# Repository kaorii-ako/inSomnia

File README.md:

# inSomnia

An adaptive, context-aware wake clock. Instead of firing at a fixed timestamp, it wakes you inside a window at a moment you are already stirring — and if you got up before the window even opened, it stays quiet.

Built for [Hack Club Forge](https://forge.hackclub.com). Firmware-first, fully offline after WiFi time sync, no cloud service, no audio leaves the device.

---

## What it actually does

| Situation | Behaviour |
|---|---|
| You're already up before the window opens | Alarm is suppressed for the day and logged as "skipped — you were already up" |
| You're carrying sleep debt | The gentle wake is held back by up to 15 min so an early stir doesn't cost you the lie-in. **The hard deadline never moves.** |
| You start stirring inside the window | Gentle wake begins immediately — soft tone ramping up over several minutes |
| You sleep right through to the hard deadline | Full-intensity alarm, no more waiting |
| A sensor dies or is unplugged | **Failsafe**: degrades to a plain fixed-time alarm at the deadline. It never fails silent. Even with no WiFi it runs on an internal fallback clock. |

### Why I made it

I hate being ripped out of deep sleep at 06:50 exactly when I was finally sleeping well, and I also hate my phone blaring when I’m already in the kitchen making coffee. Both are the same bug: a clock that knows time but not context. I wanted a clock that knows *whether I'm in bed and moving* — easily measurable with a thermal array — and uses that to pick a kinder moment inside a window, or to stay quiet if I’m already up. I built it for myself, and because a believable demo needs honest numbers, not "AI" marketing.

### The 12 keys

| | col 1 | col 2 | col 3 | col 4 |
|---|---|---|---|---|
| **row 1** (front) | `DISMISS` | `SNOOZE` | `LIGHT` | `SKIP` |
| **row 2** | `OPEN −` | `OPEN +` | `DEAD −` | `DEAD +` |
| **row 3** (back) | `PAGE` | `SOFT` | `LOUD` | `SAVE` |

Row 1 is what you hit half-asleep. Rows 2 and 3 are setup you do awake: move the window and deadline in 5-minute steps, page through status / window / sleep-debt screens, test the alarm, save to flash. Everything is also on the web UI at `http://insomnia.local`.

## How to use it — step by step

1. **Assemble** — Solder the PCB (`hardware/inSomnia.kicad_pcb`, 0805 passives, through-hole tactiles), mount the board on the 4× M2 bosses in `hardware/case/inSomnia_case.FCStd`, plug modules onto headers: J3 ST7735 TFT, J4 INMP441 mic, J5 MLX90640 thermal (aimed at the bed), J7 optional native USB.
2. **Flash** — `cd firmware && pio run -t upload` and `pio device monitor` at 115200. Requires PlatformIO + `espressif32@6.5.0`.
3. **First boot WiFi** — No credentials stored, so it opens AP `inSomnia-setup` (pass `insomnia`). Join it, open `http://192.168.4.1`, pick your network + password. Reboots and appears as `http://insomnia.local` (mDNS). If no WiFi, it still runs on a fallback clock (`*` beside time) and will still alarm at the deadline.
4. **Set your window** — On device: `OPEN ±` and `DEAD ±` move times in 5-min steps, `PAGE` to see them, `SAVE` to flash. Or on web UI: *Settings → Window opens / Hard deadline*.
5. **Sleep** — Place the clock on the nightstand with the thermal aperture aimed at the bed (within ~1.5 m, no wire to the bed). ` roi` in Settings crops the bed region if needed.
6. **Morning** — `DISMISS` stops, `SNOOZE` (= snoozeMin, default 7) resumes as hard alarm, `SKIP` is manual "don't bother tonight". Last night's sleep: `PAGE` → debt screen or web *Last night* card (TST / efficiency / WASO / SOL — labelled as estimates).
7. **Tune** — Web *Settings*: `countScale` is the one calibration — watch *Counts this epoch* overnight, set so quiet epoch ≈ 0; `Body margin` and `in-bed min pixels` for duvet thickness.

## How it decides

One sensor does most of the work:

- **MLX90640 32×24 thermal array**, on the clock, aimed at the bed.
  - *Frame-to-frame change* → a motion index. This is contactless video actigraphy, validated against polysomnography at **Cohen's κ = 0.733**, comparable to a wrist actigraph. It feeds Cole-Kripke.
  - *Warm body-sized region* → **in bed / out of bed**. Far stronger than a PIR, because it can tell you-in-the-bed from a warm object in the room.
  - No wire to the bed, and at 768 pixels you cannot identify a person from it.
- **INMP441 I2S microphone** → RMS level per epoch. A loudness hint that nudges the stirring threshold. It is a level detector, *not* a sound classifier.

An earlier version used a mattress accelerometer. It was dropped because it needs 1–2 m of I2C cable from the nightstand to the bed, and I2C is spec'd to 400 pF (≈1 m at 100 kHz) against cable that runs 100–240 pF/m.

Two separate pieces of logic sit on top, because they answer different questions:

1. **A causal 3-state machine** (asleep / stirring / awake) with hysteresis. It may only look backwards, because it drives the alarm in real time. This is a threshold heuristic — see the honesty section below.
2. **Cole-Kripke (1992)** for the morning report. It needs the two *following* epochs, so it lags 2 minutes and can never drive a live decision.

## Being honest about the "AI"

This matters more than the feature list, so it goes near the top.

**The on-device logic is not AI.** Cole-Kripke is a weighted moving average with a threshold, published in 1992. The 3-state classifier is thresholds plus hysteresis. Calling either one "AI" would be marketing, not engineering.

**Accuracy ceiling.** Actigraphy sleep/wake scoring agrees with clinical polysomnography roughly **78–80%** of the time. But its specificity for *wake* is only **0.35–0.64** — it is much better at spotting sleep than wakefulness. Sound-based staging is no better: the best published smartphone-audio model (HomeSleepNet) gets 76.2% overall and **63.4% on wake epochs**.

That single fact shaped the design. Alarm suppression is the feature most exposed to a wrong "you're awake" call, so it is **not** driven by the sleep classifier. It is driven by `outOfBed()` — no warm mass in the bed region for 3 epochs — which is close to a binary measurement rather than a 64%-accurate inference.

**This is not clinical sleep tracking.** Without EEG there is no true sleep staging. Consumer trackers systematically overestimate sleep and underestimate wake-after-sleep-onset, worst of all for people who sleep badly. The numbers in the app are estimates and are labelled as such.

**One number you must calibrate.** Cole-Kripke's weights assume ActiGraph counts, a proprietary unit. Ours are arbitrary units from your own mattress, so `countScale` in Settings divides ours into that range. The *algorithm* is validated; this *scaling* is not. Watch epoch counts overnight and set it so a quiet epoch lands near zero.

**Posture is not claimed.** The thermal array reports *movement and position*. Classifying sleeping posture under a duvet at 32×24 is a research problem — the published work that does it used an infrared **depth** camera with synthetic blanket augmentation. Movement and position are what the sleep model needs, so that is what is built and that is what it says.

**Sleep debt is an estimate built on an estimate.** Debt is `max(0, need − actual)` summed over a rolling 14 nights, which is the window research finds matters for current impairment (Van Dongen 2003: 6 h/night for 14 days ≈ two nights of total deprivation). But "actual" comes from Cole-Kripke scoring that under-reports wake — so read it as a trend, not a clinical figure.

**No trained model ships yet.** A learned audio or thermal classifier is the obvious next step, but a model needs labelled data and there is no polysomnography ground truth here to validate against. The honest path is to ship the validated heuristic, collect feature data, and only then train.

---

## Hardware

**ESP32-S3-WROOM-1-N16R8** — WiFi + BLE 5, native I2S, 8 MB PSRAM, SIMD for future MFCC work. Chosen over the ESP32-C3 because the C3 has no PSRAM and too few GPIO once an I2S microphone is added.

Schematic, pin map, BOM and wiring notes: **[`hardware/HARDWARE.md`](hardware/HARDWARE.md)**
BOM with pricing: [`hardware/inSomnia_bom.csv`](hardware/inSomnia_bom.csv) — **~$68.62 for 1 unit incl. sensors** (MLX90640 dominates)
Rendered schematic: `hardware/inSomnia_schematic.pdf` and `images/schematic.png`
Gerbers: `hardware/inSomnia_gerbers.zip` + `hardware/fab/`

> The hero image above is a **render** from the actual FreeCAD STL (`hardware/case/inSomnia_case_shell.stl`, 7,628 verts), not a photo — nothing has been fabricated yet. It is built to the same dimensions as the FreeCAD enclosure below, and the board renders come from the actual KiCad files.

### Wiring

*All modules plug onto headers — no soldering to the bed. See `hardware/HARDWARE.md` pin map for the exact GPIO table and `images/routing-front-copper.png` for the routed board.*

| Header | Module | Wires |
|---|---|---|
| J3 1×08 | ST7735 128×160 TFT | SCK 12, MOSI 11, CS 10, DC 9, RST 8, BL 13 (PWM), +3V3/GND |
| J4 1×06 | INMP441 mic (I2S) | BCLK 4, WS 5, DIN 6, +3V3/GND |
| J5 1×05 | MLX90640 32×24 thermal (I2C) | SDA 1, SCL 2 (4.7k pull-ups), +3V3/GND |
| J6 1×03 | Spare / was PIR | +5V, IO14, GND |
| J7 1×04 | Native USB | D- 19, D+ 20 |
| J1 1×02 | Power 5V in | 5V → AMS1117-3.3 → 3V3 |
| J2 1×06 | UART prog | TX/RX + EN/BOOT tactiles SW1/SW2 |

### Enclosure

Parametric case in FreeCAD: **`hardware/case/`** (STEP + STL + `.FCStd`).

- 106 × 86 × 54 mm outer, 2.5 mm walls, 101 × 81 mm cavity for the board
- Wedge profile, display face sloped 44.1°
- **36 × 29 mm display window** — a 1.8" ST7735's *active area* is only ~35 × 28 mm, much smaller than the module outline
- 12 keypad holes cut at the real SW3–SW14 coordinates from the KiCad file
- Thermal aperture, buzzer grille, rear cable exit, regulator vents, 4× M2 bosses aligning with PCB mounting holes (3.2mm NPTH)
- ~58 cm³ ≈ 72 g of PLA at full infill

FreeCAD + STEP + STL:
`hardware/case/inSomnia_case.FCStd` / `inSomnia_case_shell.step` / `inSomnia_case_shell.stl` / `inSomnia_base_plate.step`
Case views: `images/case-iso.png` `images/case-front.png` `images/case-top.png`

The FreeCAD model now embeds the PCB placement so the board sits on the bosses; the Blender render imports the STL directly so they cannot drift (replaced earlier hand-typed dimensions).

Known cosmetic issue: the keypad sits right-of-centre because that is where it is on the PCB. Fixing it means re-laying-out the board; noted for v2.

- 53 components + 4× M2 mounting holes, 41 nets, **schematic ERC clean (0 violations)**
- 100 × 80 mm two-layer board — **DRC clean, 0 violations, 0 unconnected items**
- 737 tracks, 141 vias, GND pour both layers, antenna keepout enforced
- Passives 0805, through-hole tactile buttons and headers — hand-solderable
- Gerbers + drill ready to order: `hardware/inSomnia_gerbers.zip`

Sensor modules (mic, thermal, display) mount on headers rather than being soldered down, so they can be positioned without a bed wire.

## Firmware

PlatformIO + Arduino-ESP32, pinned to `espressif32@6.5.0`.

```bash
cd firmware
pio run              # build
pio run -t upload    # flash
pio device monitor   # serial 115200 — shows [epoch] counts + state + [alarm] transitions
```

Footprint: **RAM 20.1%, Flash 13.6%** of a 16 MB part — lots of headroom. Verified 2026-09-17.

### First boot

No WiFi credentials are stored, so the device opens an access point called **`inSomnia-setup`** (password `insomnia`). Join it, open `http://192.168.4.1`, pick your network. It reboots and comes back at **`http://insomnia.local`**. Without WiFi it still runs on a fallback clock (time shows `*`) and will still alarm at the hard deadline — it never fails silent.

The web UI gives you the live clock and sleep state, tonight's alarm status, last night's report, live sensor readings (thermal heatmap 32×24, mic RMS/dBFS), and every threshold as an editable setting. Everything stays on your own network — no audio ever leaves the device.

### Layout

```
firmware/
  include/ src/
    main.cpp          loop, epoch tick (60s), display render, 12-key handling
    settings.*        NVS-persisted config (window, thresholds, debt)
    net.*             WiFi STA + setup AP, NTP, mDNS, fallback clock
    web_ui.*          HTTP server, dashboard, JSON API (/api/state, /api/thermal, /api/settings)
    display.*         ST7735 128x160 SPI via GPIO matrix
    buzzer.*          LEDC tone + volume (gentle ramp → hard)
    key_matrix.*      74HC165 chain, debounce, edge latch (12 keys)
    thermal.*         MLX90640 -> motion index, in-bed detection, centroid
    mic.*             INMP441 I2S -> RMS / dBFS / loud fraction per epoch
    sleep_model.*     Cole-Kripke + causal 3-state classifier (asleep/stirring/awake)
    sleep_debt.*      rolling 14-night debt, recency-weighted
    alarm.*           window, suppression, escalation, debt shift, failsafe, snooze
```

Debug mode: serial log each epoch + web *Live* cards show raw `counts`, `warm pixels`, `motion index`, `RMS`, `state`; thresholds are live-editable.

## PCB

`hardware/inSomnia.kicad_pcb` — **100 × 80 mm**, 2 layer, rounded 3 mm corners.
**DRC clean: 0 violations, 0 unconnected items.**

| | |
|---|---|
| Components | 53 (+4 holes), zero courtyard overlaps |
| Tracks | 737 segments @ 0.20 mm |
| Vias | 141 @ 0.30 mm drill / 0.60 mm pad |
| Copper | GND pour on both layers, islands auto-removed |
| Clearance | 0.20 mm |
| Mounting | 4× 3.2mm NPTH at corners → M2 bosses in case |

Fabrication files are in `fab/`, zipped as `inSomnia_gerbers.zip` (Gerbers + Excellon drill + drill map + BOM).

### Layout

- **Top-left** — ESP32-S3 module, antenna pointing off the top edge
- **Top-right** — sensor and display headers in a row (J3 TFT, J4 mic, J5 thermal, J6 spare, J7 USB)
- **Right** — 4 × 3 keypad on a 11 × 12 mm grid
- **Left-centre** — 74HC165 chain and the 12 key pull-ups
- **Bottom-left** — 5 V in, regulator, bulk caps
- **Bottom-centre** — buzzer and its transistor driver

### Two things to know before ordering

**1. The antenna keepout is intentional.** A rule area at x 2–50 mm, y 0–6.25 mm keeps copper, tracks and vias out from under the module's antenna, and the courtyard deliberately overhangs the top board edge. DRC flags that overhang as a boundary violation — that is correct RF practice, not a mistake. Verified: no track or via crosses the keepout.

**2. There are twelve 0.20 mm holes, and they are not mine.** Every via I placed is 0.30 mm. The 0.20 mm holes are the thermal vias built into the stock `RF_Module:ESP32-S3-WROOM-1` footprint, under the module's ground pad. Many budget fab processes have a **0.30 mm minimum drill**, so this may trigger an upcharge or a rejection. Two options:

- Order from a fab that allows 0.20 mm (costs a little more), or
- Delete the twelve pad-41 thermal vias — fine for a hand-built prototype, since the module's ground still connects through the main pad and the GND pour.

The board has **not been fabricated or bench-tested**. It is DRC-clean, which means the geometry is self-consistent — not that the design is proven. Sanity-checked in `#forge` and via KiCad/FreeCAD MCP.

## Known gaps

- No trained sound-event model yet (see honesty section).
- Cole-Kripke `countScale` ships with a placeholder default and needs per-bed tuning.
- The PCB has not been fabricated or bench-tested; it is DRC-checked, not proven.
- The WROOM footprint contributes twelve 0.20 mm thermal vias; some budget fabs require 0.30 mm minimum. See `hardware/HARDWARE.md` for the two ways round it.
- No physical build yet — next step is printing the case and soldering the board, then adding build photos + demo video for the "shipping" submission.

## References

- [Comparison and Validation of Actigraphy Algorithms Using a Large Community Dataset (JMIR Formative Research, 2025)](https://formative.jmir.org/2025/1/e70778)
- [Actigraphy-based sleep estimation in adolescents and adults (PubMed)](https://pubmed.ncbi.nlm.nih.gov/29403321/)
- [Prediction of Sleep Stages Via Deep Learning Using Smartphone Audio Recordings — HomeSleepNet (JMIR, 2023)](https://www.jmir.org/2023/1/e46216)
- [End-to-End Sleep Staging Using Nocturnal Sounds (Nature and Science of Sleep, 2022)](https://www.dovepress.com/end-to-end-sleep-staging-using-nocturnal-sounds-from-microphone-chips--peer-reviewed-fulltext-article-NSS)
- [Accuracy of 11 Wearable, Nearable, and Airable Consumer Sleep Trackers (JMIR mHealth, 2023)](https://mhealth.jmir.org/2023/1/e50983)
- [Video-Based Actigraphy for Monitoring Wake and Sleep (Sensors, 2019)](https://doi.org/10.3390/s19051075)
- [A Blanket Accommodative Sleep Posture Classification System Using an Infrared Depth Camera (2021)](https://www.ncbi.nlm.nih.gov/pmc/articles/PMC8402261/)
- [Human Occupancy Monitoring with an Infrared Thermal Array Sensor](https://www.ncbi.nlm.nih.gov/pmc/articles/PMC11722904/)
- [I²C Cabling — bus capacitance and length limits (Analog Devices)](https://www.analog.com/en/technical-articles/i2c-cabling.html)

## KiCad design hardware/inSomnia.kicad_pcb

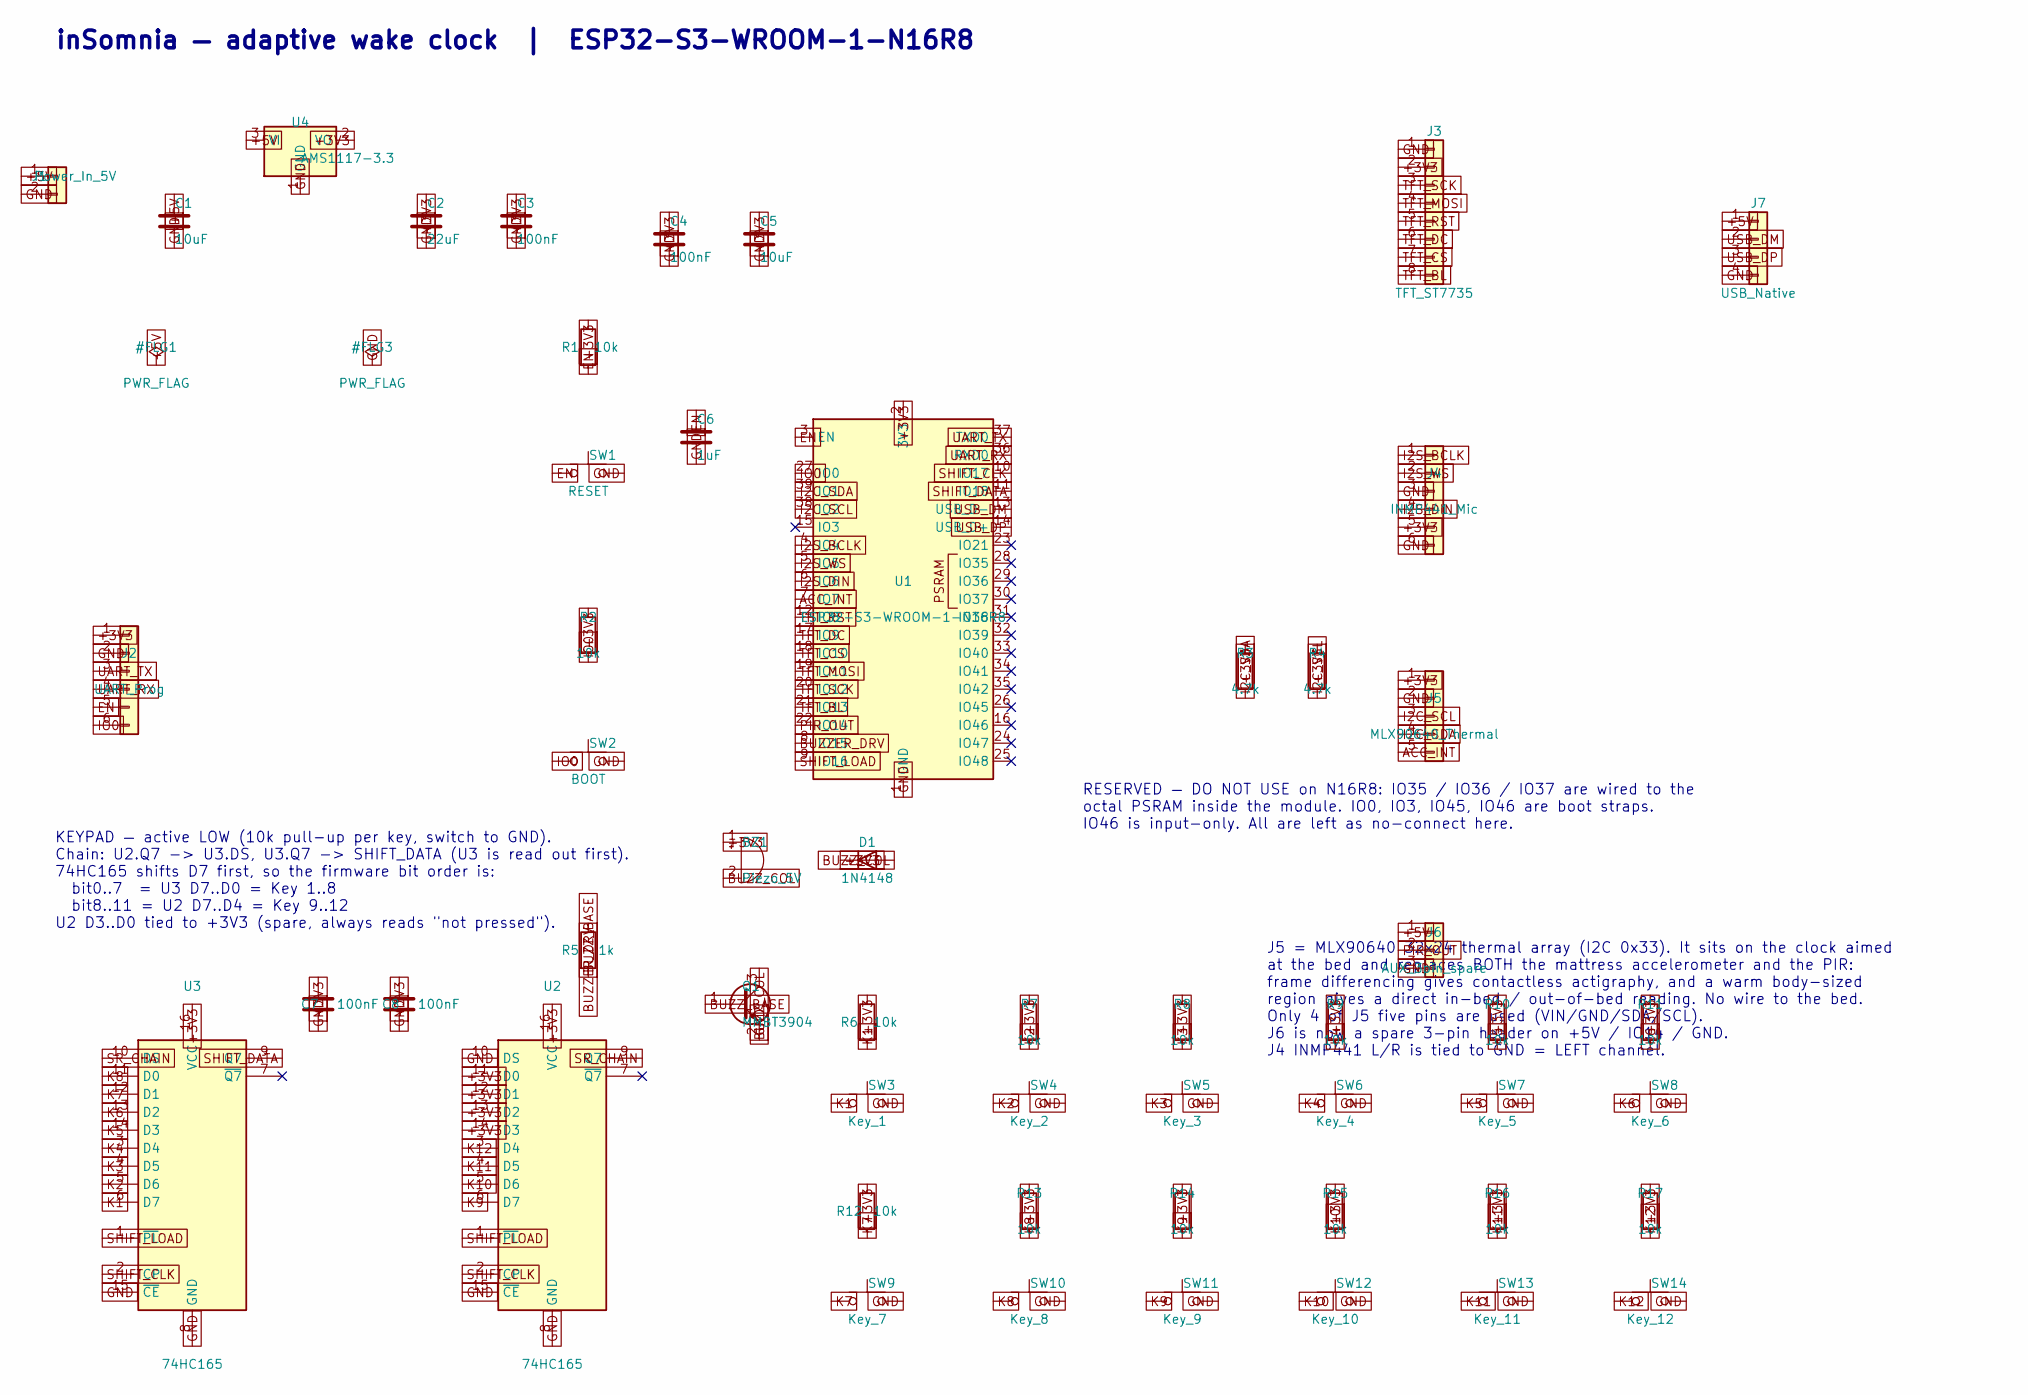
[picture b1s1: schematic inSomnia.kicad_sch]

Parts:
BZ1: Piezo_5V; Buzzer_TDK_PS1240P02BT_D12.2mm_H6.5mm
C1, C5: 10uF; C_0805_2012Metric
C2: 22uF; C_0805_2012Metric
C3, C4, C7, C8: 100nF; C_0805_2012Metric
C6: 1uF; C_0805_2012Metric
D1: 1N4148; D_SOD-123
J1: Power_In_5V; PinHeader_1x02_P2.54mm_Vertical
J2: UART_Prog; PinHeader_1x06_P2.54mm_Vertical
J3: TFT_ST7735; PinHeader_1x08_P2.54mm_Vertical
J4: INMP441_Mic; PinHeader_1x06_P2.54mm_Vertical
J5: MLX90640_Thermal; PinHeader_1x05_P2.54mm_Vertical
J6: AUX_3pin_spare; PinHeader_1x03_P2.54mm_Vertical
J7: USB_Native; PinHeader_1x04_P2.54mm_Vertical
Q1: MMBT3904; SOT-23
R1, R2, R6, R7, R8, R9, R10, R11, R12, R13, R14, R15, R16, R17: 10k; R_0805_2012Metric
R3, R4: 4.7k; R_0805_2012Metric
R5: 1k; R_0805_2012Metric
SW1: RESET; SW_PUSH_6mm
SW2: BOOT; SW_PUSH_6mm
SW3: Key_1; SW_PUSH_6mm
SW4: Key_2; SW_PUSH_6mm
SW5: Key_3; SW_PUSH_6mm
SW6: Key_4; SW_PUSH_6mm
SW7: Key_5; SW_PUSH_6mm
SW8: Key_6; SW_PUSH_6mm
SW9: Key_7; SW_PUSH_6mm
SW10: Key_8; SW_PUSH_6mm
SW11: Key_9; SW_PUSH_6mm
SW12: Key_10; SW_PUSH_6mm
SW13: Key_11; SW_PUSH_6mm
SW14: Key_12; SW_PUSH_6mm
U1: ESP32-S3-WROOM-1-N16R8; ESP32-S3-WROOM-1
U2, U3: 74HC165; SOIC-16_3.9x9.9mm_P1.27mm
U4: AMS1117-3.3; SOT-223-3_TabPin2

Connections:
+3V3: BZ1.1 (+), C2.1, C3.1, C4.1, C5.1, C7.1, C8.1, D1.1 (K), J2.1, J3.2, J4.5, J5.1, R1.1, R2.1, R3.1, R4.1, R6.1, R7.1, R8.1, R9.1, R10.1, R11.1, R12.1, R13.1, R14.1, R15.1, R16.1, R17.1, U1.2 (3V3), U2.11 (D0), U2.12 (D1), U2.13 (D2), U2.14 (D3), U2.16 (VCC), U3.16 (VCC), U4.2 (VO)
+5V: C1.1, J1.1, J6.1, J7.1, U4.3 (VI)
ACC_INT: J5.5, U1.7 (IO7)
BUZZER_DRV: R5.1, U1.8 (IO15)
BUZZ_BASE: Q1.1 (B), R5.2
BUZZ_COL: BZ1.2 (-), D1.2 (A), Q1.3 (C)
EN: C6.1, J2.5, R1.2, SW1.1, U1.3 (EN)
GND: C1.2, C2.2, C3.2, C4.2, C5.2, C6.2, C7.2, C8.2, J1.2, J2.2, J3.1, J4.3, J4.6, J5.2, J6.3, J7.4, Q1.2 (E), SW1.2, SW2.2, SW3.2, SW4.2, SW5.2, SW6.2, SW7.2, SW8.2, SW9.2, SW10.2, SW11.2, SW12.2, SW13.2, SW14.2, U1.1 (GND), U1.33 (IO40), U1.40 (GND), U1.41 (GND), U2.8 (GND), U2.10 (DS), U2.15 (~CE), U3.8 (GND), U3.15 (~CE), U4.1 (GND)
I2C_SCL: J5.3, R4.2, U1.38 (IO2)
I2C_SDA: J5.4, R3.2, U1.39 (IO1)
I2S_BCLK: J4.1, U1.4 (IO4)
I2S_DIN: J4.4, U1.6 (IO6)
I2S_WS: J4.2, U1.5 (IO5)
IO0: J2.6, R2.2, SW2.1, U1.27 (IO0)
K1: R6.2, SW3.1, U3.6 (D7)
K2: R7.2, SW4.1, U3.5 (D6)
K3: R8.2, SW5.1, U3.4 (D5)
K4: R9.2, SW6.1, U3.3 (D4)
K5: R10.2, SW7.1, U3.14 (D3)
K6: R11.2, SW8.1, U3.13 (D2)
K7: R12.2, SW9.1, U3.12 (D1)
K8: R13.2, SW10.1, U3.11 (D0)
K9: R14.2, SW11.1, U2.6 (D7)
K10: R15.2, SW12.1, U2.5 (D6)
K11: R16.2, SW13.1, U2.4 (D5)
K12: R17.2, SW14.1, U2.3 (D4)
PIR_OUT: J6.2, U1.22 (IO14)
SHIFT_CLK: U1.10 (IO17), U2.2 (CP), U3.2 (CP)
SHIFT_DATA: U1.11 (IO18), U1.16 (IO46), U3.9 (Q7)
SHIFT_LOAD: U1.9 (IO16), U2.1 (~PL), U3.1 (~PL)
SR_CHAIN: U2.9 (Q7), U3.10 (DS)
TFT_BL: J3.8, U1.21 (IO13)
TFT_CS: J3.7, U1.18 (IO10)
TFT_DC: J3.6, U1.17 (IO9)
TFT_MOSI: J3.4, U1.19 (IO11), U1.23 (IO21)
TFT_RST: J3.5, U1.12 (IO8)
TFT_SCK: J3.3, U1.20 (IO12)
UART_RX: J2.4, U1.36 (RXD0)
UART_TX: J2.3, U1.37 (TXD0)
USB_DM: J7.2, U1.13 (USB_D-)
USB_DP: J7.3, U1.14 (USB_D+)

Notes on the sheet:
inSomnia — adaptive wake clock | ESP32-S3-WROOM-1-N16R8
RESERVED — DO NOT USE on N16R8: IO35 / IO36 / IO37 are wired to the octal PSRAM inside the module. IO0, IO3, IO45, IO46 are boot straps. IO46 is input-only. All are left as no-connect here.
KEYPAD — active LOW (10k pull-up per key, switch to GND). Chain: U2.Q7 -> U3.DS, U3.Q7 -> SHIFT_DATA (U3 is read out first). 74HC165 shifts D7 first, so the firmware bit order is: bit0..7 = U3 D7..D0 = Key 1..8 bit8..11 = U2 D7..D4 = Key 9..12 U2 D3..D0 tied to +3V3 (spare, always reads "not presse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
J5 = MLX90640 32x24 thermal array (I2C 0x33). It sits on the clock aimed at the bed and replaces BOTH the mattress accelerometer and the PIR: frame differencing gives contactless actigraphy, and a warm body-sized region gives a direct in-bed / out-of-bed reading. No wire to the bed. Only 4 of J5 fi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

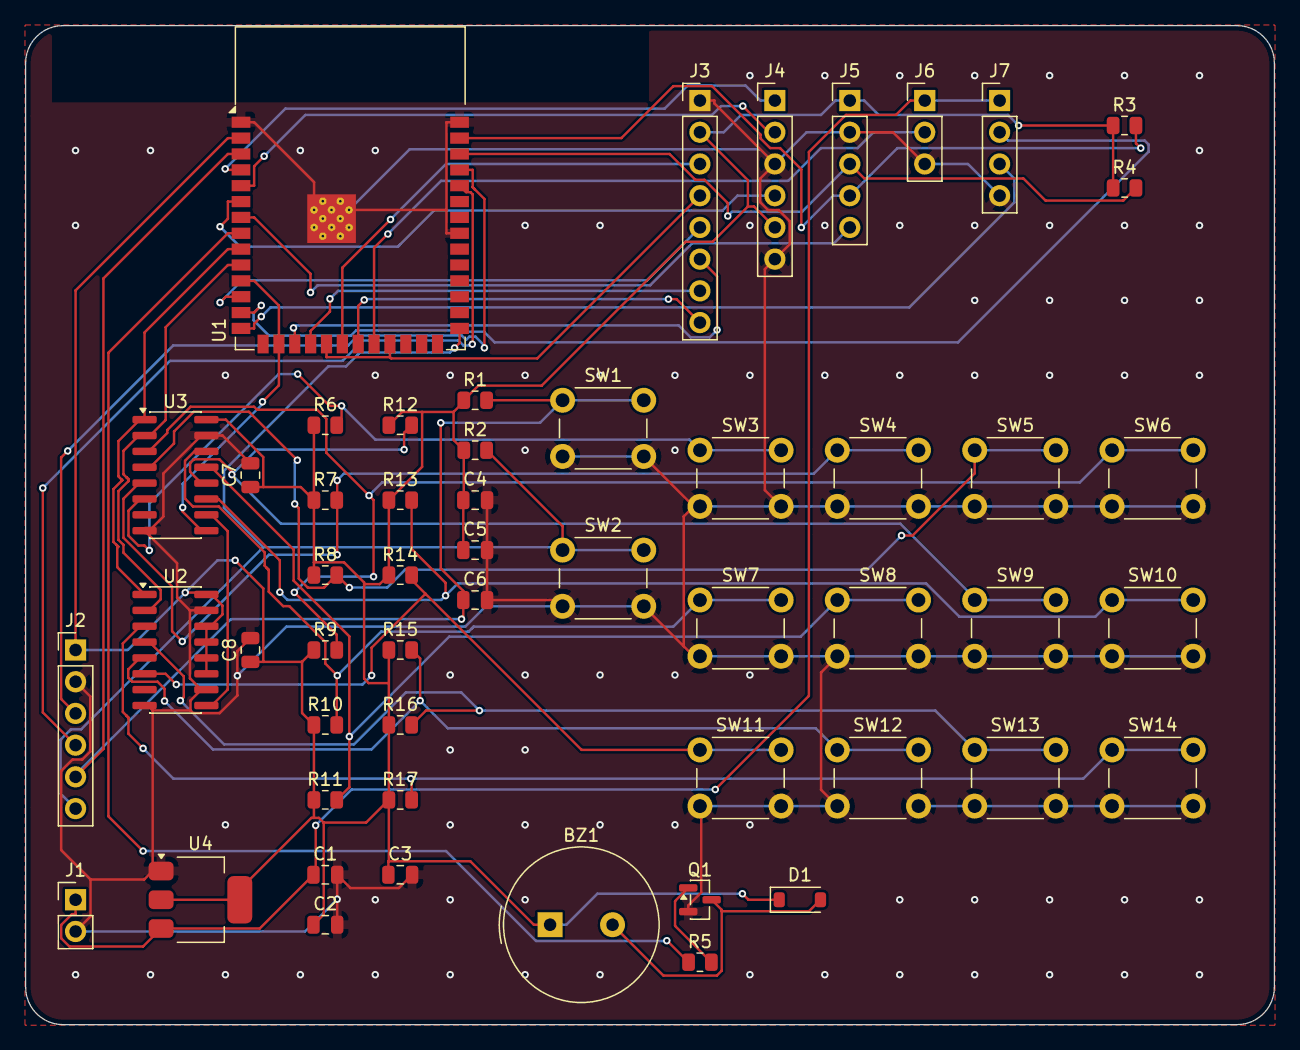
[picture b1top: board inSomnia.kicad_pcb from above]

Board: 2 copper layers, 100.0 x 80.0 mm, 53 parts (0 on the bottom side), 41 nets.

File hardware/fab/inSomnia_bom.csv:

"Refs","Value","Footprint","Qty"
"BZ1","Piezo_5V","Buzzer_Beeper:Buzzer_TDK_PS1240P02BT_D12.2mm_H6.5mm","1"
"C1,C5","10uF","Capacitor_SMD:C_0805_2012Metric","2"
"C2","22uF","Capacitor_SMD:C_0805_2012Metric","1"
"C3,C4,C7,C8","100nF","Capacitor_SMD:C_0805_2012Metric","4"
"C6","1uF","Capacitor_SMD:C_0805_2012Metric","1"
"D1","1N4148","Diode_SMD:D_SOD-123","1"
"J1","Power_In_5V","Connector_PinHeader_2.54mm:PinHeader_1x02_P2.54mm_Vertical","1"
"J2","UART_Prog","Connector_PinHeader_2.54mm:PinHeader_1x06_P2.54mm_Vertical","1"
"J3","TFT_ST7735","Connector_PinHeader_2.54mm:PinHeader_1x08_P2.54mm_Vertical","1"
"J4","INMP441_Mic","Connector_PinHeader_2.54mm:PinHeader_1x06_P2.54mm_Vertical","1"
"J5","MLX90640_Thermal","Connector_PinHeader_2.54mm:PinHeader_1x05_P2.54mm_Vertical","1"
"J6","AUX_3pin_spare","Connector_PinHeader_2.54mm:PinHeader_1x03_P2.54mm_Vertical","1"
"J7","USB_Native","Connector_PinHeader_2.54mm:PinHeader_1x04_P2.54mm_Vertical","1"
"Q1","MMBT3904","Package_TO_SOT_SMD:SOT-23","1"
"R1,R2,R6-R17","10k","Resistor_SMD:R_0805_2012Metric","14"
"R3,R4","4.7k","Resistor_SMD:R_0805_2012Metric","2"
"R5","1k","Resistor_SMD:R_0805_2012Metric","1"
"SW1","RESET","Button_Switch_THT:SW_PUSH_6mm","1"
"SW2","BOOT","Button_Switch_THT:SW_PUSH_6mm","1"
"SW3","Key_1","Button_Switch_THT:SW_PUSH_6mm","1"
"SW4","Key_2","Button_Switch_THT:SW_PUSH_6mm","1"
"SW5","Key_3","Button_Switch_THT:SW_PUSH_6mm","1"
"SW6","Key_4","Button_Switch_THT:SW_PUSH_6mm","1"
"SW7","Key_5","Button_Switch_THT:SW_PUSH_6mm","1"
"SW8","Key_6","Button_Switch_THT:SW_PUSH_6mm","1"
"SW9","Key_7","Button_Switch_THT:SW_PUSH_6mm","1"
"SW10","Key_8","Button_Switch_THT:SW_PUSH_6mm","1"
"SW11","Key_9","Button_Switch_THT:SW_PUSH_6mm","1"
"SW12","Key_10","Button_Switch_THT:SW_PUSH_6mm","1"
"SW13","Key_11","Button_Switch_THT:SW_PUSH_6mm","1"
"SW14","Key_12","Button_Switch_THT:SW_PUSH_6mm","1"
"U1","ESP32-S3-WROOM-1-N16R8","RF_Module:ESP32-S3-WROOM-1","1"
"U2,U3","74HC165","Package_SO:SOIC-16_3.9x9.9mm_P1.27mm","2"
"U4","AMS1117-3.3","Package_TO_SOT_SMD:SOT-223-3_TabPin2","1"

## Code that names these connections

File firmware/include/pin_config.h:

#pragma once

// inSomnia pin map — ESP32-S3-WROOM-1-N16R8
// Matches hardware/inSomnia.kicad_sch (ERC clean).
//
// RESERVED, never assign on the N16R8 part:
//   IO35 / IO36 / IO37  -> octal PSRAM inside the module
//   IO0 / IO3 / IO45 / IO46 -> boot straps (IO46 is also input-only)
//   IO19 / IO20 -> native USB D-/D+
// All of the above are left as no-connect on the schematic.

// ── TFT ST7735 128x160 (SPI, remapped via the GPIO matrix) ────────
#define TFT_SCK     12
#define TFT_MOSI    11
#define TFT_CS      10
#define TFT_DC      9
#define TFT_RST     8
#define TFT_BL      13

// ── INMP441 I2S MEMS microphone ──────────────────────────────────
#define I2S_BCLK    4
#define I2S_WS      5
#define I2S_DIN     6
#define I2S_PORT    I2S_NUM_0

// ── MLX90640 32x24 thermal array (I2C) ───────────────────────────
// Sits on the clock, aimed at the bed. Replaces both the mattress
// accelerometer and the PIR: it gives contactless actigraphy AND a direct
// in-bed / out-of-bed measurement, with no wire running to the bed.
#define I2C_SDA       1
#define I2C_SCL       2
#define THERM_INT     7    // spare, MLX90640 breakout does not need it
#define MLX90640_ADDR 0x33

// ── Spare (was PIR; the thermal array supersedes it) ─────────────
#define AUX_GPIO    14

// ── Buzzer (via MMBT3904 NPN, active high) ───────────────────────
#define BUZZER_PIN  15

// ── 74HC165 keypad shift chain ───────────────────────────────────
#define SHIFT_LOAD  16
#define SHIFT_CLK   17
#define SHIFT_DATA  18

// ── Panel geometry ───────────────────────────────────────────────
#define TFT_PANEL_W     128
#define TFT_PANEL_H     160
#define TFT_ROTATION    1     // landscape -> 160 wide x 128 tall

// ── LEDC ─────────────────────────────────────────────────────────
// timer = (channel / 2) % 4, so channels 0 and 1 share timer 0.
// Backlight must not share a timer with the buzzer.
#define BUZZER_CHANNEL       0   // timer 0
#define BACKLIGHT_CHANNEL    2   // timer 1
#define BUZZER_RESOLUTION    8
#define BUZZER_IDLE_FREQ     2000
#define BACKLIGHT_FREQ       5000
#define BACKLIGHT_RESOLUTION 8

// ── Keypad ───────────────────────────────────────────────────────
// Chain: U2.Q7 -> U3.DS, U3.Q7 -> SHIFT_DATA. U3 is clocked out first,
// and the 74HC165 presents D7 first, so:
//   bit0..7  = U3 D7..D0 = Key 1..8
//   bit8..11 = U2 D7..D4 = Key 9..12
#define NUM_SHIFT_REGS   2
#define NUM_KEY_BITS     (NUM_SHIFT_REGS * 8)
#define NUM_KEYS         12
#define KEY_ACTIVE_LOW   1
#define KEY_DEBOUNCE_MS  25

// ── PIR sampling (Phase 1 proxy; Phase 3 replaces the classifier) ──
#define PIR_SAMPLE_INTERVAL_MS  1000
#define PIR_WINDOW_SAMPLES      300
